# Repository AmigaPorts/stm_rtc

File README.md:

# STM32 emulator of msm6264b RTC for Amiga computers

This project aims to implement RTC replacement for classic Amiga computers.
Target uC was chosen to be as cheap as possible, easily available & RoHS-friendly.
This project may work on other computers, but it's not guaranteed.

If you made it work for other machine with some fix or without it,
tell me so by creating an issue!

## Build and flash

To build firmware, you'll need STM32CubeMX installed to generate required HAL stuff.
This way you can also easily port this project to other chips.

- Delete `build` folder if present in main repo directory.
- Delete `makefile` if present in main repo directory.
  For some reason STM32CubeMX doesn't regenerate it each time.
- Open stm_rtc_yourPartName.ioc in STM32CubeMX, then click `GENERATE CODE` button.
- After that, simply use generated makefile by writing:

``` sh
make OPT="-Ofast -std=c11 -Wpedantic -frename-registers" DEBUG=0
```

If you're on Windows and have MinGW installed, you may use `mingw32-make` instead.
This should generate firmware in `./build/stm_rtc.bin`.
I've used following GCC version:

``` plain
> arm-none-eabi-gcc --version
arm-none-eabi-gcc (GNU Tools for ARM Embedded Processors) 5.4.1 20160919 (release) [ARM/embedded-5-branch revision 240496]
```

To flash firmware into your STM you'll need `stm32flash` tool installed.
Required pinout is as follows:

``` plain
PA14 (TX) - USB-UART RX
PA15 (RX) - USB-UART TX
BOOT0     - 3v3 during programming, GND when run
RES       - 3v3 via 10k or any other resistor
```

You may need to drive RES for a short time to GND to reset device before programming.

Connect UART-USB dongle to your PC and type:

``` sh
stm32flash -R -w ./build/stm_rtc_stm32f031k4u.bin COM5
# or
stm32flash -R -w ./build/stm_rtc_stm32f030c6t.bin COM5
```

Of course replace COM5 with name of correct serial port.
You may use Realterm, Cutecom or whatever serial monitor you prefer to list them.

## How it works

TBD

## License

See each file for details.

- All ST code is under STMicroelectronics's license.
- MSM RTC emulation code found in `msm_rtc.c` and `msm_rtc.h` is licensed under [Mozilla Public License 2.0](LICENSE).

## TODO

- write
- add pinout compatibility with smaller stm32f0 packages
- port to  STM32F031C6T6
- PCB
- switch to LL generation for less footprint?
- compat with latest arm gcc?
- stm32f030 power saving code for even cheaper device?

## This worked on QFP48

``` asm
 147              	.L5:
 148 001c 0B69     		ldr	r3, [r1, #16]
 149 001e 1340     		ands	r3, r2
 150 0020 FCD1     		bne	.L5
 151 0022 3869     		ldr	r0, [r7, #16]
 152 0024 050A     		lsrs	r5, r0, #8
 153 0026 3540     		ands	r5, r6
 154 0028 A800     		lsls	r0, r5, #2
 155 002a 6546     		mov	r5, ip
 156 002c 2858     		ldr	r0, [r5, r0]
 157 002e 4546     		mov	r5, r8
 158 0030 6061     		str	r0, [r4, #20]
 159 0032 2560     		str	r5, [r4]
 160 0034 2360     		str	r3, [r4]
 161 0036 F1E7     		b	.L5
```

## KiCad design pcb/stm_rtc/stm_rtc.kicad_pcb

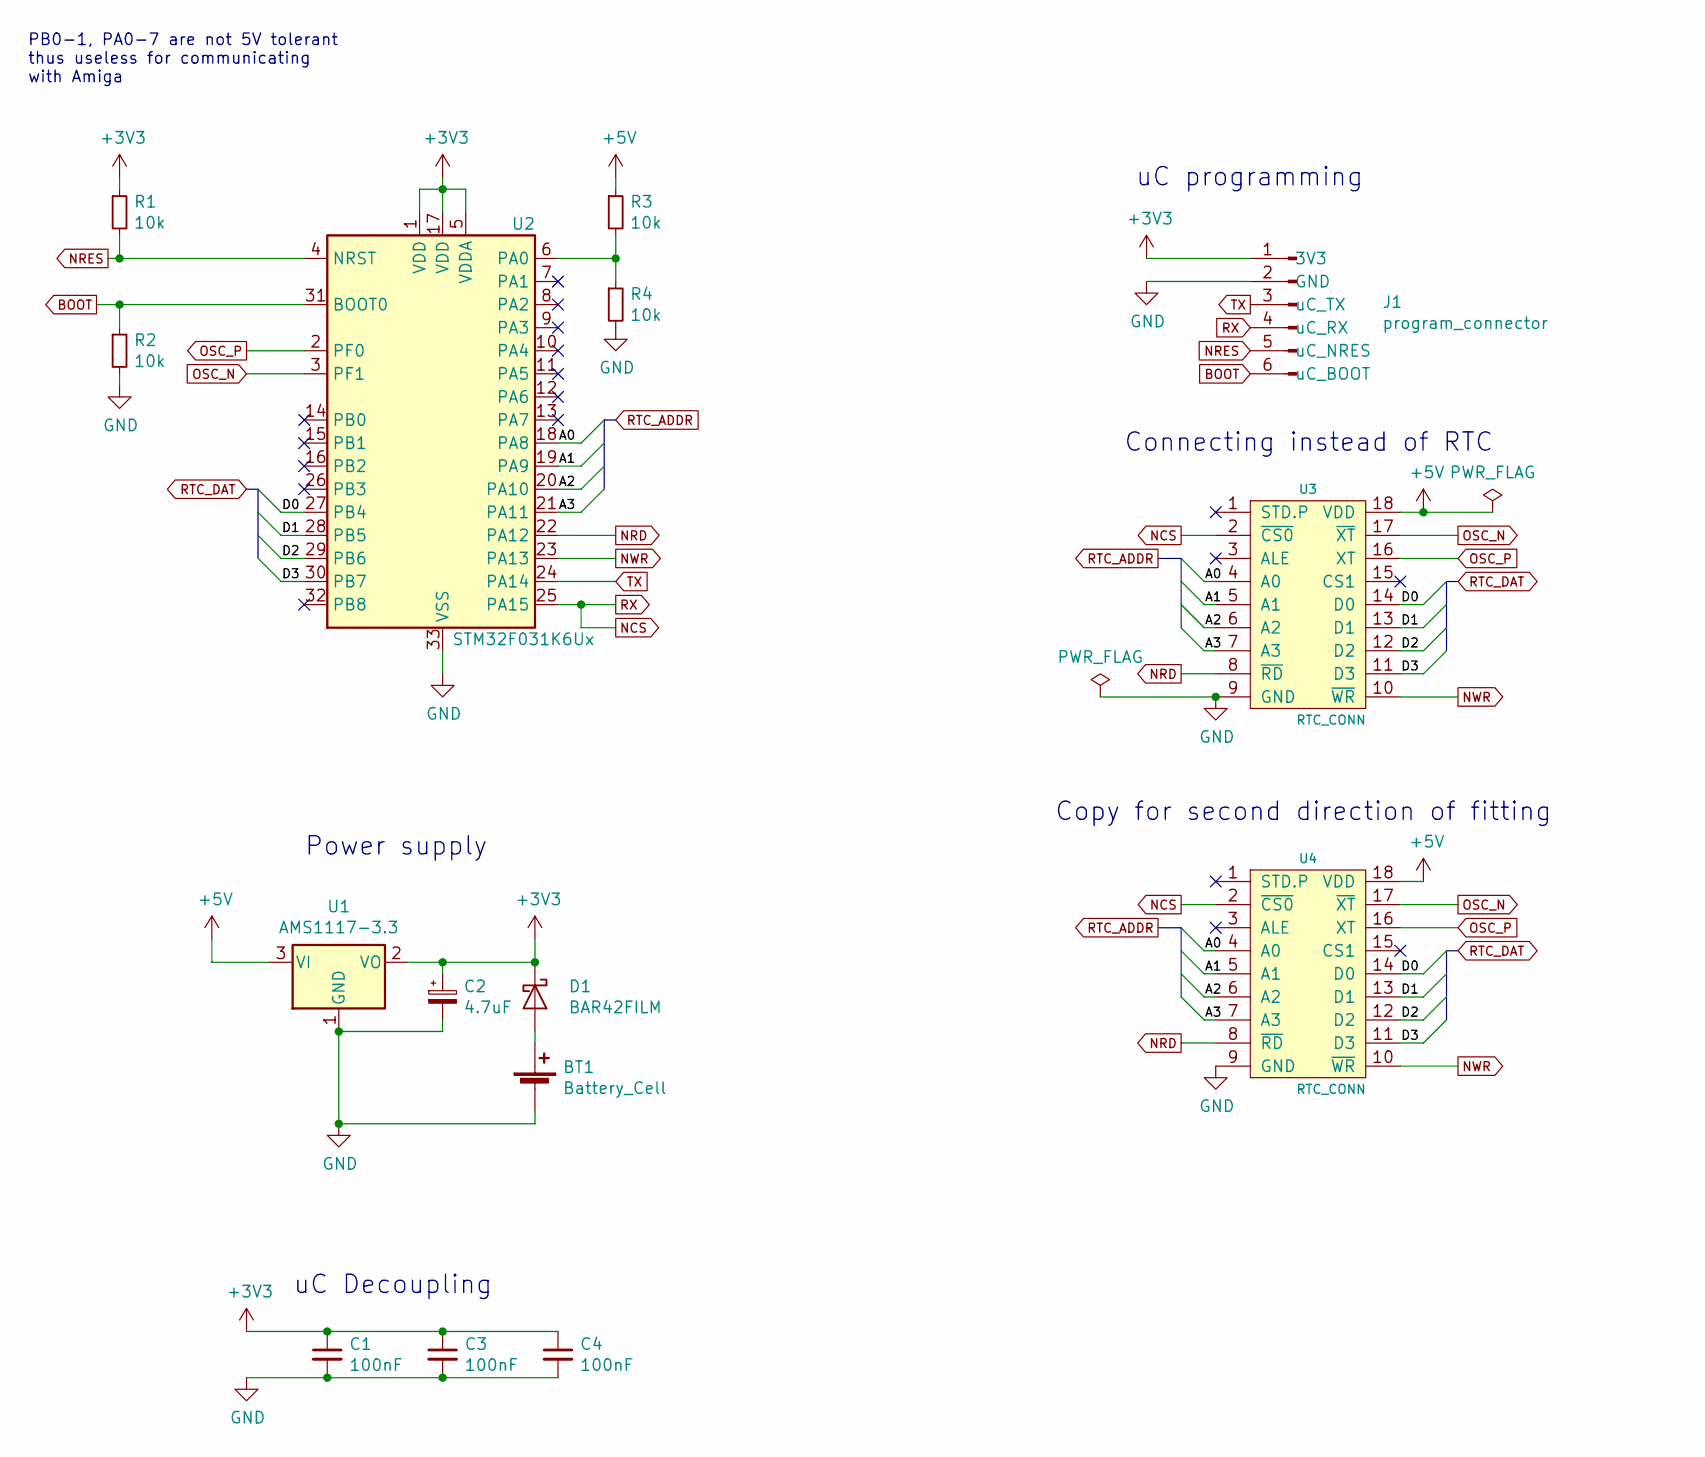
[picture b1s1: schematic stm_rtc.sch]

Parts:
BT1: Battery_Cell; BatteryHolder_Keystone_106_1x20mm
C1, C3, C4: 100nF; C_0805_2012Metric_Pad1.15x1.40mm_HandSolder
C2: 4.7uF; C_0805_2012Metric_Pad1.15x1.40mm_HandSolder
D1: BAR42FILM; SOT-23
J1: program_connector; PinHeader_1x06_P2.54mm_Vertical
R1, R2, R3, R4: 10k; R_0805_2012Metric_Pad1.15x1.40mm_HandSolder
U1: AMS1117-3.3; SOT-223-3_TabPin2
U2: STM32F031K6Ux; QFN-32-1EP_5x5mm_P0.5mm_EP3.45x3.45mm
U3, U4: RTC_CONN; DIP-18_W7.62mm

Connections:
+3V3: C1.1, C2.1, C3.1, C4.1, D1.3 (K), J1.1 (3V3), R1.1, U1.2 (VO), U2.1 (VDD), U2.5 (VDDA), U2.17 (VDD)
+5V: R3.1, U1.3 (VI), U3.18 (VDD), U4.18 (VDD)
/A0: U2.18 (PA8), U3.4 (A0), U4.4 (A0)
/A1: U2.19 (PA9), U3.5 (A1), U4.5 (A1)
/A2: U2.20 (PA10), U3.6 (A2), U4.6 (A2)
/A3: U2.21 (PA11), U3.7 (A3), U4.7 (A3)
/D0: U2.27 (PB4), U3.14 (D0), U4.14 (D0)
/D1: U2.28 (PB5), U3.13 (D1), U4.13 (D1)
/D2: U2.29 (PB6), U3.12 (D2), U4.12 (D2)
/D3: U2.30 (PB7), U3.11 (D3), U4.11 (D3)
BOOT: J1.6 (uC_BOOT), R2.1, U2.31 (BOOT0)
GND: BT1.2 (-), C1.2, C2.2, C3.2, C4.2, J1.2 (GND), R2.2, R4.2, U1.1 (GND), U2.33 (VSS), U3.9 (GND), U4.9 (GND)
NCS: J1.4 (uC_RX), U2.25 (PA15), U3.2 (~CS0), U4.2 (~CS0)
NRD: U2.22 (PA12), U3.8 (~RD), U4.8 (~RD)
NRES: J1.5 (uC_NRES), R1.2, U2.4 (NRST)
NWR: U2.23 (PA13), U3.10 (~WR), U4.10 (~WR)
unnamed: BT1.1 (+), D1.1 (A)
unnamed: R3.2, R4.1, U2.6 (PA0)
OSC_N: U2.3 (PF1), U3.17 (~XT), U4.17 (~XT)
OSC_P: U2.2 (PF0), U3.16 (XT), U4.16 (XT)
TX: J1.3 (uC_TX), U2.24 (PA14)

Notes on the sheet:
uC Decoupling
PB0-1, PA0-7 are not 5V tolerant thus useless for communicating with Amiga
Power supply
uC programming
Connecting instead of RTC
Copy for second direction of fitting

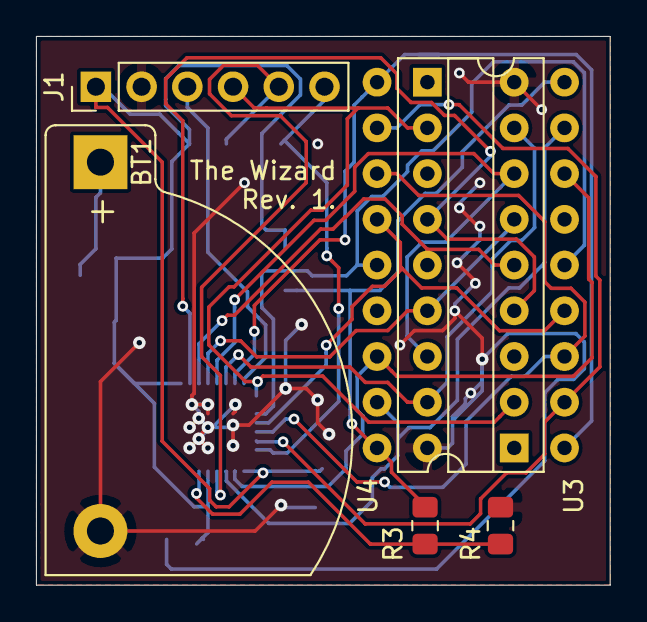
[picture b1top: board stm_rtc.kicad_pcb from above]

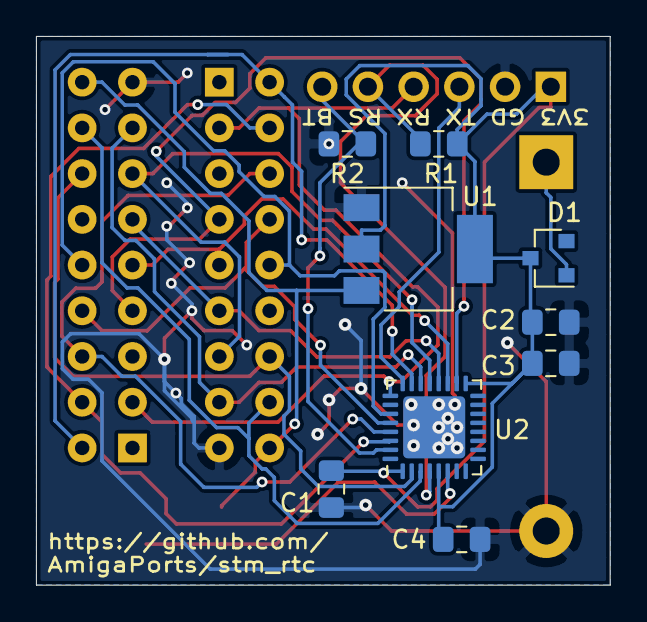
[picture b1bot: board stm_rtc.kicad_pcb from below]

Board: 2 copper layers, 31.9 x 30.5 mm, 15 parts (9 on the bottom side), 21 nets.

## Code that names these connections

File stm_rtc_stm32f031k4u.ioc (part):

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Mcu.Name=STM32F031K(4-6)Ux
Mcu.Package=UFQFPN32
Mcu.UserName=STM32F031K4Ux
PA10.GPIOParameters=GPIO_Label
PA10.GPIO_Label=A2
PA10.Signal=GPIO_Input
PA11.GPIOParameters=GPIO_Label
PA11.GPIO_Label=A3
PA11.Signal=GPIO_Input
PA12.GPIOParameters=GPIO_Label
PA12.GPIO_Label=NRD
PA12.Signal=GPIO_Input
PA13.GPIOParameters=GPIO_Label
PA13.GPIO_Label=NWR
PA13.Signal=GPIO_Input
PA14.Mode=Asynchronous
PA14.Signal=USART1_TX
PA15.GPIOParameters=GPIO_Label
PA15.GPIO_Label=NCS
PA15.Signal=GPIO_Input
PA3.Mode=Asynchronous
PA3.Signal=USART1_RX
PA8.GPIOParameters=GPIO_Label
PA8.GPIO_Label=A0
PA8.Signal=GPIO_Input
PA9.GPIOParameters=GPIO_Label
PA9.GPIO_Label=A1
PA9.Signal=GPIO_Input
PB4.GPIOParameters=GPIO_Label
PB4.GPIO_Label=D0
PB4.Signal=GPIO_Input
PB5.GPIOParameters=GPIO_Label
PB5.GPIO_Label=D1
PB5.Signal=GPIO_Input
PB6.GPIOParameters=GPIO_Label
PB6.GPIO_Label=D2
PB6.Signal=GPIO_Input
PB7.GPIOParameters=GPIO_Label
PB7.GPIO_Label=D3
PB7.Signal=GPIO_Input
RCC.SYSCLKFreq_VALUE=48000000
RCC.SYSCLKSource=RCC_SYSCLKSOURCE_PLLCLK
board=custom

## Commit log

2019-06-25 pcb rev1
2019-06-26 vscode
2019-06-26 ported to STM32F031K4U
2020-09-03 vscode config
2020-09-03 tried to write asm by hand
2020-09-03 added some datasheet references
2020-09-03 added some files to gitignore
2020-09-03 added stm32g0 config
2020-09-03 stm32g0 tweaks, further migrating code
2020-09-03 made soures more portable
